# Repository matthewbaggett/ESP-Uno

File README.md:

# ESPUno - A dirty ESP8266 Arduino Uno clone

Using an ESP8266 should be fun! These processors are cheap enough to be disposable, lets make that easier to achieve as a hobbist.

Features: 

+ 80/160Mhz ESP8266
+ 5 working ADC pins (A0 is the 0-1 volt ESP8266 ADC, A1-A5 are provided by an i2c ADC controller (ADS1115) 
+ Pin 13 LED still present, tied to SCLK/GPIO6
+ LiPo cell support on-board! MCP73831 Charger circuit, TSP61200 Boost converter (shamelessly stolen from a [Sparkfun reference design](https://www.sparkfun.com/products/11231)) 
+ 3.3V regulator ([AMS1117](http://www.aliexpress.com/premium/ams1117.html?ltype=wholesale&SearchText=ams1117&d=y&origin=y&initiative_id=SB_20151010010621&isViewCP=y&catId=0))
+ All the associated recommended pullups as per the [Arduino ESP8266 project](https://github.com/esp8266/Arduino) ([Schematic](https://github.com/esp8266/Arduino/blob/esp8266/docs/ESP_improved_stability.png))
+ Built-in USB programmer ([FTDI FT232R](http://www.aliexpress.com/premium/FT232R.html?spm=2114.01020208.0.312.zEmQlv&site=glo&g=y&SortType=price_asc&SearchText=FT232R&isUnitPrice=y&initiative_id=SB_20151010010739&shipCountry=uk&needQuery=n)) similar to how the Arduinos have.
+ Mini-USB port. They're easier to get hold of, for me, and the full-size USB connector tends to short out cheaply made boards that ride up on top of the Arduino. Also should help reduce the deck height of the board.
+ All of the parts that weren't restricted to being tiny ICs (Damn ADS1115, TSP61200, LMV358IDGKR) are massive 1206-size parts.
+ Lots of amusing LEDs along the top left corner/edge. In order: Charging/Power On/RX/TX/Pin 13 "L"
+ Flash and Reset pushbuttons.

# Licence

<br />This work is licensed under a <a rel="license" href="http://creativecommons.org/licenses/by-nc/4.0/">Creative Commons Attribution-NonCommercial 4.0 International License</a>.

May be re-licenced on request.

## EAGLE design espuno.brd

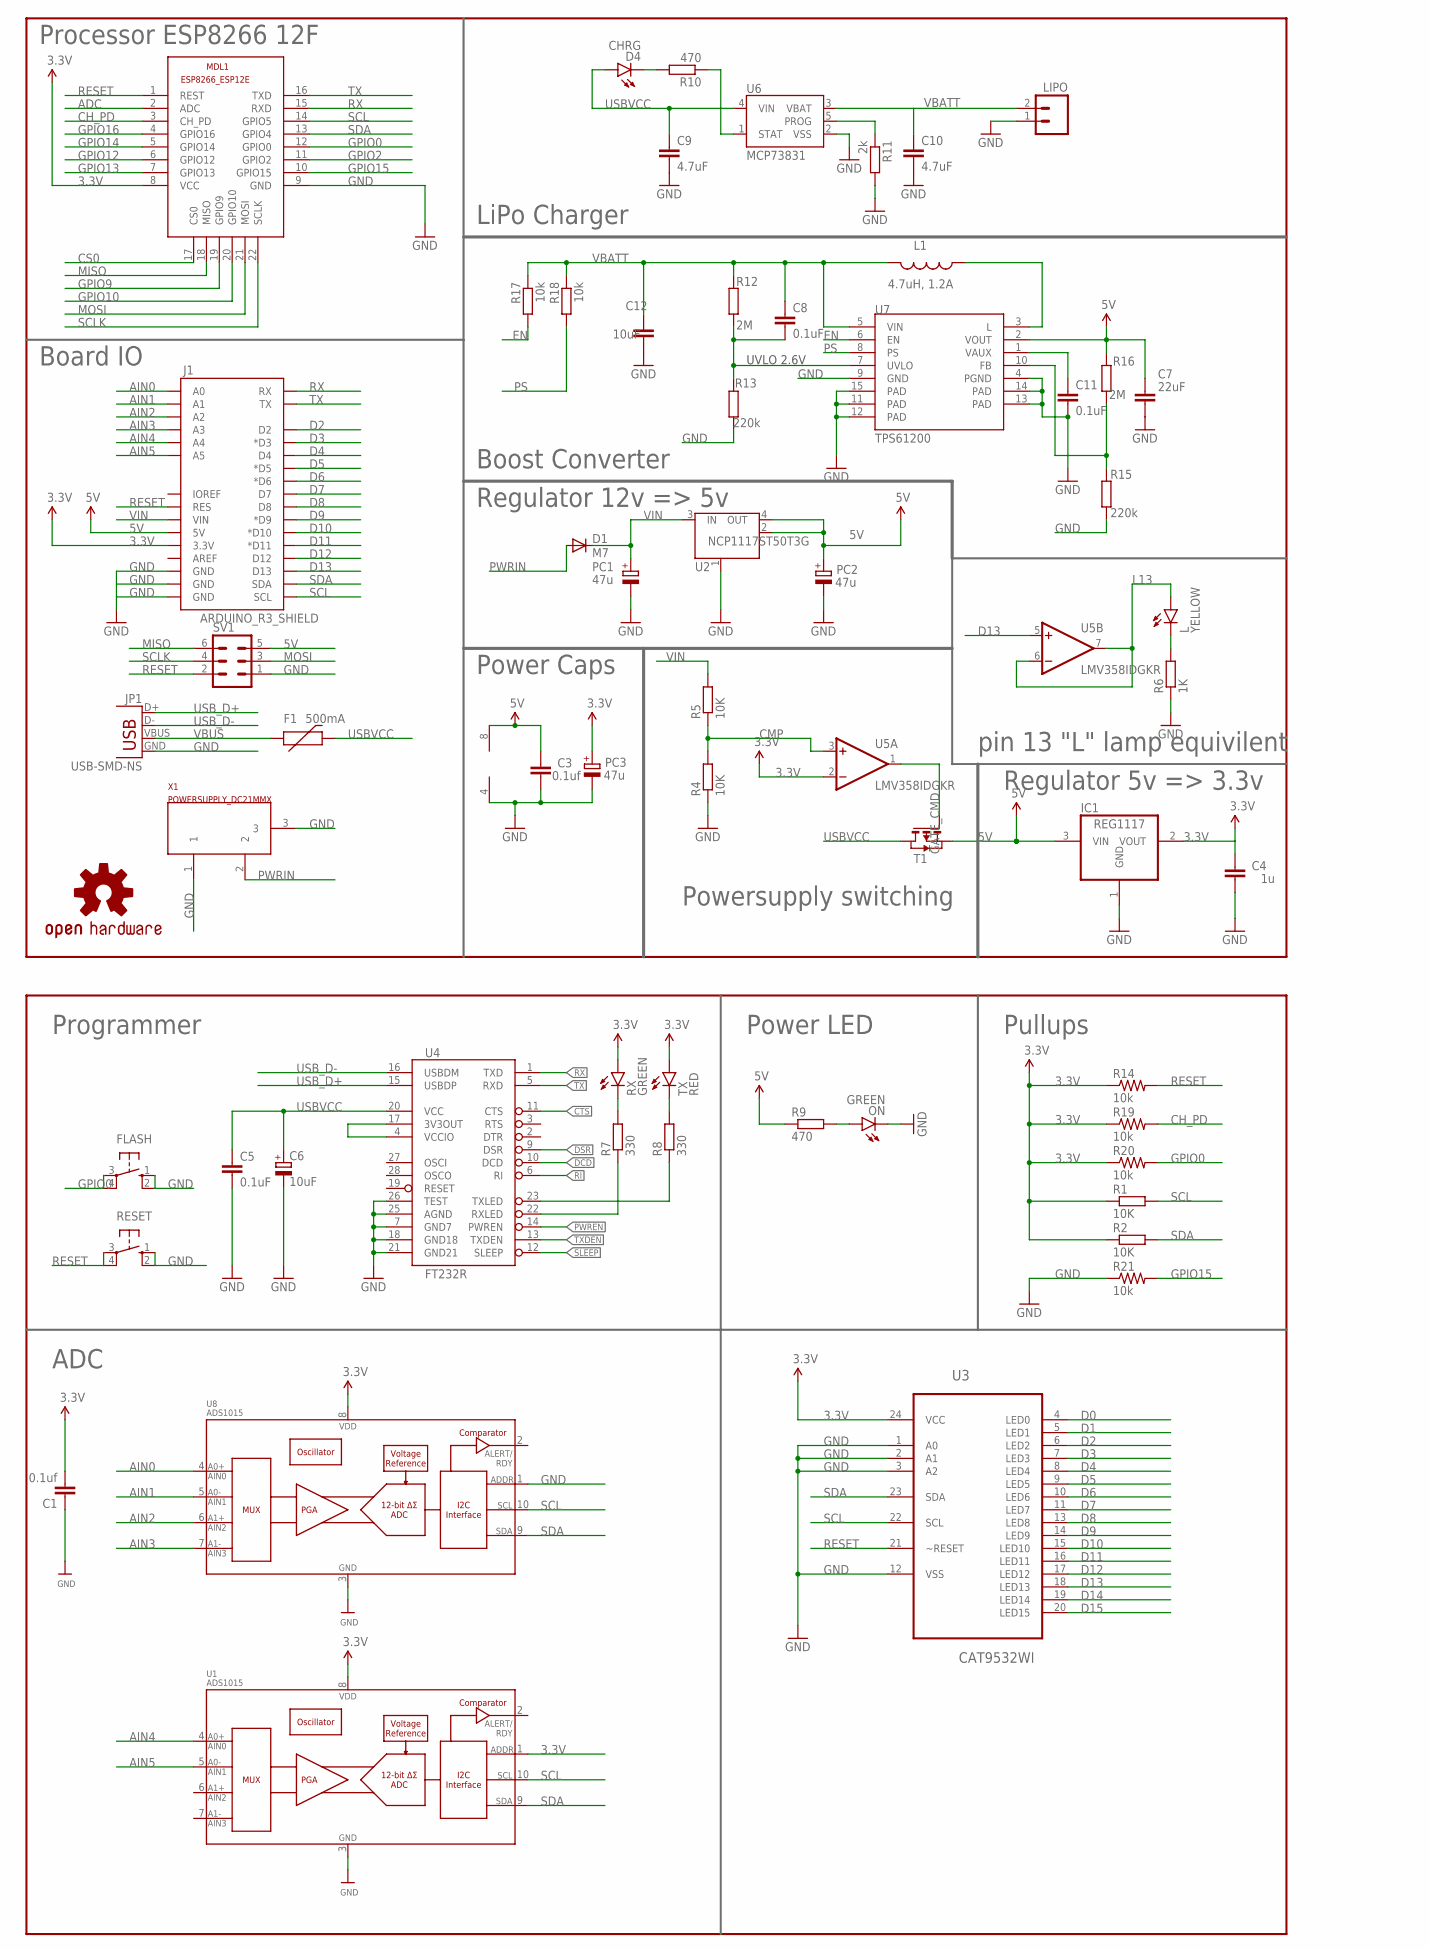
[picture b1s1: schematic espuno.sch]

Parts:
C1: 0.1uf; 1206
C3: 0.1uf; C1206K
C4: 1u; C1206K
C5, C8, C11: 0.1uF; C1206K
C6: 10uF; SMC_A
C7: 22uF; C1206K
C9, C10: 4.7uF; C1206K
C12: 10uF; C1206K
D1: M7; SMB
D4: CHRG; LED-1206
F1: 500mA; PTC-1206
FLASH: 10-XX; B3F-10XX
FRAME1, FRAME2: FRAME-LETTERNO_PACKAGE; DUMMY
IC1: REG1117; SOT223
J1: ARDUINO_R3_SHIELD; UNO_R3_SHIELD
JP1: USB-SMD-NS; USB-MINIB-NOSTOP
L: YELLOW; LED-1206
L1: 4.7uH, 1.2A; CDRH2D09
LIPO: M02JST-PTH-2; JST-2-PTH
LOGO1: OSHW-LOGOS; OSHW-LOGO-S
MDL1: ESP8266-12EESP8266-ESP12E; ESP8266-ESP12E
ON: GREEN; LED-1206
PC1, PC2, PC3: 47u; PANASONIC_D
R1, R2, R4, R5: 10K; M1206
R6: 1K; M1206
R7, R8: 330; M1206
R9, R10: 470; M1206
R11: 2k; M1206
R12, R16: 2M; M1206
R13, R15: 220k; M1206
R14, R19, R20, R21: 10k; 1206
R17, R18: 10k; M1206
RESET: 10-XX; B3F-10XX
RX: GREEN; LED-1206
SV1: MA03-2
T1: FDN340P; SOT-23
TX: RED; LED-1206
U1, U8: ADS1015; MSOP10
U2: NCP1117ST50T3G; SOT223
U3: CAT9532WI; SOIC127P1031X265-24N
U4: FT232R; SSOP28DB
U5: LMV358IDGKR; MSOP08
U6: MCP73831; SOT23-5
U7: TPS61200; QFN-10_PAD
X1: POWERSUPPLY_DC21MMX; POWERSUPPLY_DC-21MM

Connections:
3.3V: C1.2, C4.2, IC1.2 (VOUT), J1.3.3V, MDL1.8 (VCC), PC3.+, R1.1, R2.1, R14.1, R19.1, R20.1, RX.A, TX.A, U1.1 (ADDR), U1.8 (VDD), U3.24 (VCC), U5.2 (-IN), U8.8 (VDD)
5V: C3.2, C7.1, IC1.3 (VIN), J1.5V, PC2.+, R9.1, R16.2, SV1.5, T1.2 (S), U2.2 (OUT), U2.4 (OUT), U5.8 (V+), U7.2 (VOUT)
ADC: MDL1.2 (ADC)
AIN0: J1.A0, U8.4 (AIN0)
AIN1: J1.A1, U8.5 (AIN1)
AIN2: J1.A2, U8.6 (AIN2)
AIN3: J1.A3, U8.7 (AIN3)
AIN4: J1.A4, U1.4 (AIN0)
AIN5: J1.A5, U1.5 (AIN1)
CH_PD: MDL1.3 (CH_PD), R19.2
CMP: R4.2, R5.1, U5.3 (+IN)
CS0: MDL1.17 (CS0)
CTS: U4.11 (CTS)
D0: U3.4 (LED0)
D1: U3.5 (LED1)
D2: J1.D2, U3.6 (LED2)
D3: J1.D3 (*D3), U3.7 (LED3)
D4: J1.D4, U3.8 (LED4)
D5: J1.D5 (*D5), U3.9 (LED5)
D6: J1.D6 (*D6), U3.10 (LED6)
D7: J1.D7, U3.11 (LED7)
D8: J1.D8, U3.13 (LED8)
D9: J1.D9 (*D9), U3.14 (LED9)
D10: J1.D10 (*D10), U3.15 (LED10)
D11: J1.D11 (*D11), U3.16 (LED11)
D12: J1.D12, U3.17 (LED12)
D13: J1.D13, U3.18 (LED13), U5.5 (+IN)
D14: U3.19 (LED14)
D15: U3.20 (LED15)
DCD: U4.10 (DCD)
DSR: U4.9 (DSR)
EN: R17.2, U7.6 (EN)
FB: R15.2, R16.1, U7.10 (FB)
GATE_CMD: T1.3 (G), U5.1 (OUT)
GND: C1.1, C3.1, C4.1, C5.2, C6.-, C7.2, C9.2, C10.2, C11.2, C12.2, FLASH.1 (S), FLASH.2 (S1), IC1.1 (GND), J1.GND@0 (GND), J1.GND@1 (GND), J1.GND@2 (GND), JP1.GND, LIPO.1, MDL1.9 (GND), ON.C, PC1.-, PC2.-, PC3.-, R4.1, R6.1, R11.2, R13.1, R15.1, R21.1, RESET.1 (S), RESET.2 (S1), SV1.1, U1.3 (VSS), U2.1 (GND/ADJ), U3.1 (A0), U3.2 (A1), U3.3 (A2), U3.12 (VSS), U4.7 (GND7), U4.18 (GND18), U4.21 (GND21), U4.25 (AGND), U4.26 (TEST), U5.4 (V-), U6.2 (VSS), U7.4 (PGND), U7.9 (GND), U7.11 (PAD), U7.12 (PAD), U7.13 (PAD), U7.14 (PAD), U7.15 (PAD), U8.1 (ADDR), U8.3 (VSS), X1.1, X1.3
GPIO0: FLASH.3, FLASH.4 (P1), MDL1.12 (GPIO0), R20.2
GPIO2: MDL1.11 (GPIO2)
GPIO9: MDL1.19 (GPIO9)
GPIO10: MDL1.20 (GPIO10)
GPIO12: MDL1.6 (GPIO12)
GPIO13: MDL1.7 (GPIO13)
GPIO14: MDL1.5 (GPIO14)
GPIO15: MDL1.10 (GPIO15), R21.2
GPIO16: MDL1.4 (GPIO16)
L13: L.A, U5.6 (-IN), U5.7 (OUT)
MISO: MDL1.18 (MISO), SV1.6
MOSI: MDL1.21 (MOSI), SV1.3
unnamed: ON.A, R9.2
unnamed: L.C, R6.2
unnamed: R7.2, RX.C
unnamed: R8.2, TX.C
unnamed: L1.P$1 (1), U7.3 (L)
unnamed: C11.1, U7.1 (VAUX)
unnamed: R7.1, U4.22 (RXLED)
unnamed: D4.C, R10.2
unnamed: R8.1, U4.23 (TXLED)
unnamed: U4.4 (VCCIO), U4.17 (3V3OUT)
unnamed: R11.1, U6.5 (PROG)
unnamed: R10.1, U6.1 (STAT)
PS: R18.2, U7.8 (PS)
PWREN: U4.14 (PWREN)
PWRIN: D1.A, X1.2
RESET: J1.RES, MDL1.1 (REST), R14.2, RESET.3, RESET.4 (P1), SV1.2, U3.21 (~RESET)
RI: U4.6 (RI)
RX: J1.RX, MDL1.15 (RXD), U4.1 (TXD)
SCL: J1.SCL, MDL1.14 (GPIO5), R1.2, U1.10 (SCL), U3.22 (SCL), U8.10 (SCL)
SCLK: MDL1.22 (SCLK), SV1.4
SDA: J1.SDA, MDL1.13 (GPIO4), R2.2, U1.9 (SDA), U3.23 (SDA), U8.9 (SDA)
SLEEP: U4.12 (SLEEP)
TX: J1.TX, MDL1.16 (TXD), U4.5 (RXD)
TXDEN: U4.13 (TXDEN)
USBVCC: C5.1, C6.+, C9.1, D4.A, F1.2, T1.1 (D), U4.20 (VCC), U6.4 (VIN)
USB_D+: JP1.D+, U4.15 (USBDP)
USB_D-: JP1.D-, U4.16 (USBDM)
UVLO: C8.2, R12.1, R13.2, U7.7 (UVLO)
VBATT: C8.1, C10.1, C12.1, L1.P$2 (2), LIPO.2, R12.2, R17.1, R18.1, U6.3 (VBAT), U7.5 (VIN)
VBUS: F1.1, JP1.VBUS
VIN: D1.C, J1.VIN, PC1.+, R5.2, U2.3 (IN)

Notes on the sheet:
UVLO 2.6V
Programmer
ADC
Power LED
Pullups
pin 13 "L" lamp equivilent
Processor ESP8266 12F
Board IO
Regulator 5v => 3.3v
Powersupply switching
Power Caps
Regulator 12v => 5v
Boost Converter
LiPo Charger

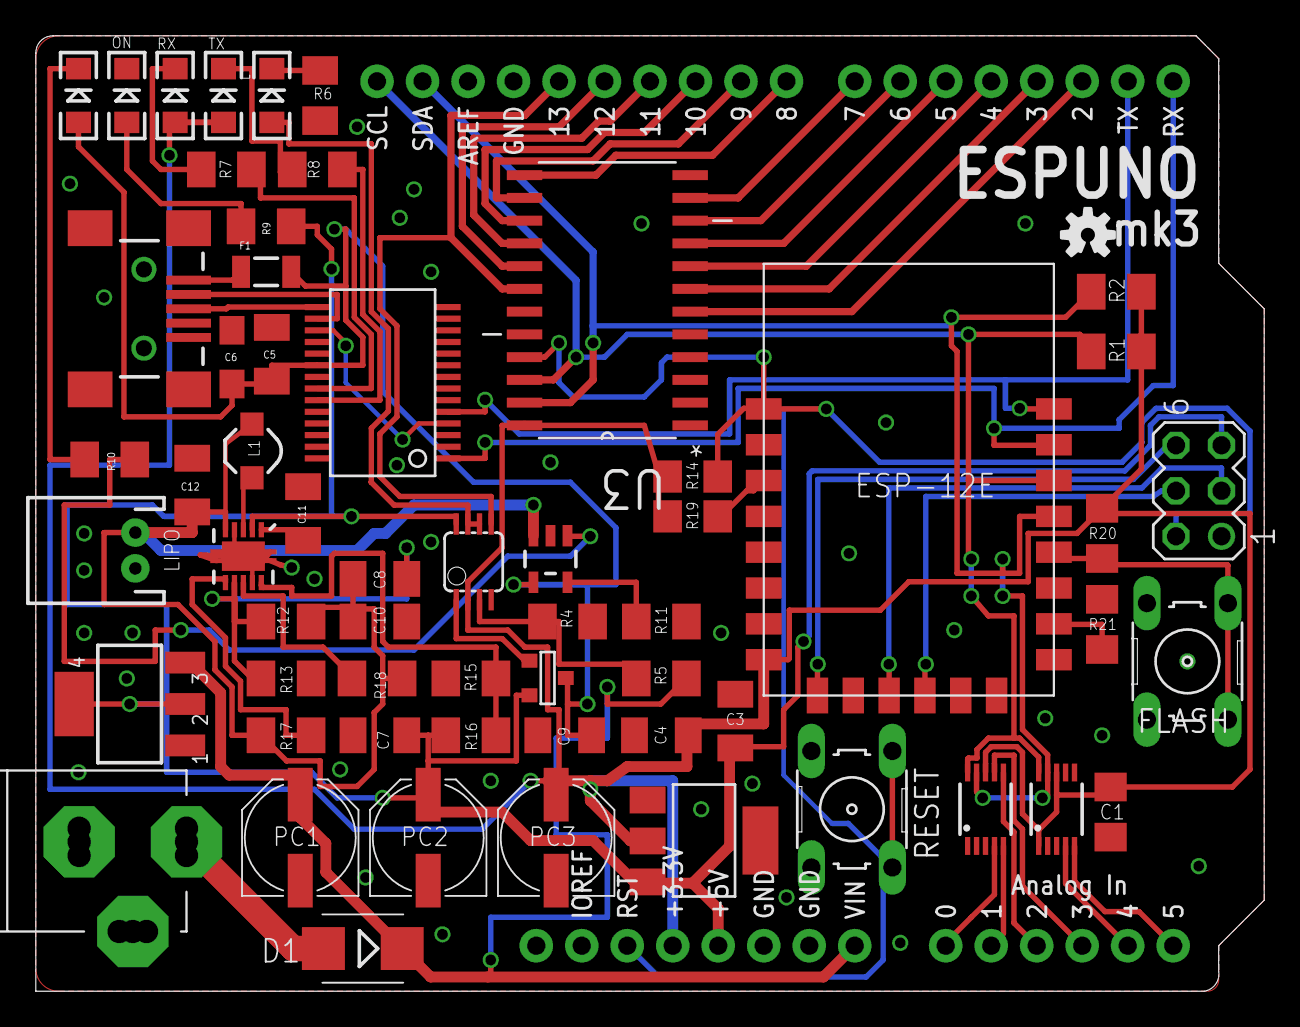
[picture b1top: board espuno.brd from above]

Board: 2 copper layers, 68.6 x 53.3 mm, 63 parts (0 on the bottom side), 58 nets.

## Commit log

2015-08-27 Added LIPO parts, use more 0805 resistors/caps and 1206 LEDs instead of f&cking 0402s
2015-09-04 Fixing layout of labels, adding ESPUNO text, slight layout tweaks to make slightly more pleasing.
2015-09-10 Adding BOM
2015-10-07 Espuno Mk2, with bigass 1206's for errything
2015-10-09 removed because old
2015-10-09 Mk2 revision complete. Tidied schematics and board. Added pullups.
2015-10-09 Move some labels, change 'CHARGING' into 'CHRG' for brevity
2015-10-09 No changes?
2015-10-09 Revise which size C1 is
2015-10-09 Change 100nf => 0.1uf
2015-10-10 Fix dpi
2015-10-10 Move i2c pullup resistors to Pullups section of schematic
2015-10-10 Better rear silkscreen layer
2015-11-04 Fix bug with TX/RX switched, renumber PC1,PC3,PC4 to be PC1-3 in order of decreasing voltage rail.
2015-11-04 Change puny 3.3v regulator for a 800mA-1A regulator. Rearrangements to make space, remove redundent capacitor
2015-11-04 Use two ADS1015's and a CAT9531 to interface with the outside world.
2015-11-05 move adc bits up a bit away from the port
2015-11-06 Make the FT232R consume its own 3.3v so I can test it by merely attaching USB.
2015-11-06 Add 500mA fuse

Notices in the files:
parts and their libraries:
SparkFun-LED: Licensing: CC v3.0 Share-Alike You are welcome to use this library for commercial purposes.
SparkFun-Connectors: Licensing: Creative Commons ShareAlike 4.0 International - https://creativecommons.org/licenses/by-sa/4.0
SparkFun-Aesthetics: Released under the Creative Commons
